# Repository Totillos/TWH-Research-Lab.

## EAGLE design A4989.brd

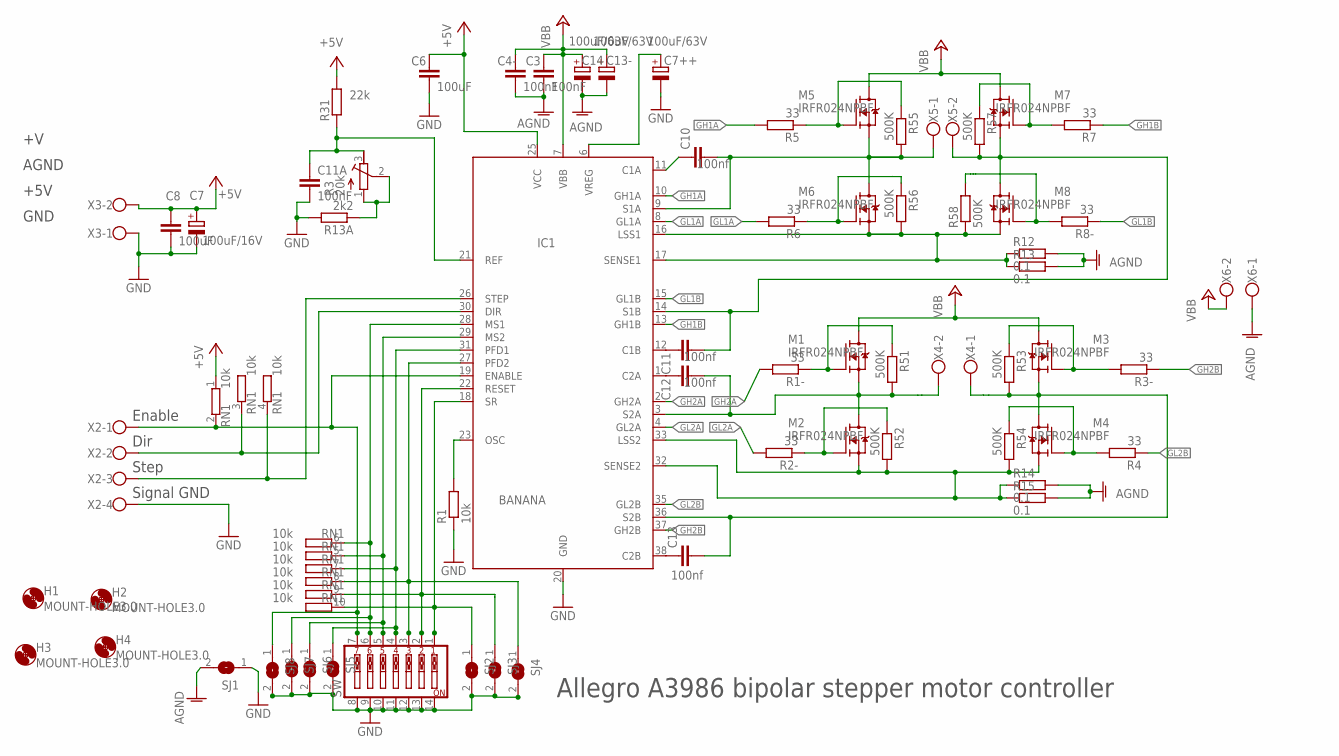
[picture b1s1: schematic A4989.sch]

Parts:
C3, C4-, C11A: 100nF; C0805
C6, C8: 100uF; C0805
C7: 100uF/16V; E5-10,5
C7++: 100uF/63V; E2-5
C10, C11, C12, C13: 100nf; C0805
C13-, C14: 100uF/63V; E5-10,5
H1, H2, H3, H4: MOUNT-HOLE3.0; 3,0
IC1: BANANA; TSSOP38
M1, M2, M3, M4, M5, M6, M7, M8: IRFR024NPBF; DPAK
R1: 10k; M0805
R1-, R2-, R3-, R4, R5, R6, R7, R8-: 33; R0805
R3: 20k; RTRIM64W
R12, R13, R14, R15: 0.1; R2512
R13A: 2k2; M0805
R31: 22k; M0805
R51, R52, R53, R54, R55, R56, R57, R58: 500K; R0805
RN1: 10k; SIL10
SJ1, SJ2, SJ3, SJ4, SJ5, SJ6, SJ7, SJ8: SJ
SW: SW_DIP-7; EDG-07
X2: W237-4
X3, X4, X5, X6: W237-102

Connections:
+5V: C6.1, C7.+, C8.1, IC1.25 (VCC), R31.2, RN1.1, X3.2
+24V: C3.1, C4-.1, C13-.+, C14.+, IC1.7 (VBB), M1.4 (D), M3.4 (D), M5.4 (D), M7.4 (D), X6.2
AGND: C3.2, C4-.2, C13-.-, C14.-, R12.2, R13.2, R14.2, R15.2, SJ1.2, X6.1
GH1A: IC1.10 (GH1A), R5.2
GH1B: IC1.13 (GH1B), R7.1
GH2A: IC1.2 (GH2A), R1-.2
GH2B: IC1.37 (GH2B), R3-.1
GL1A: IC1.8 (GL1A), R6.2
GL1B: IC1.15 (GL1B), R8-.1
GL2A: IC1.4 (GL2A), R2-.2
GL2B: IC1.35 (GL2B), R4.1
GND: C6.2, C7.-, C7++.-, C8.2, C11A.2, IC1.20 (GND), R1.1, R13A.2, SJ1.1, SJ2.2, SJ3.2, SJ4.2, SJ5.2, SJ6.2, SJ7.2, SJ8.2, SW.8, SW.9, SW.10, SW.11, SW.12, SW.13, SW.14, X2.4, X3.1
unnamed: IC1.27 (PFD2), RN1.8 (2), SJ4.1, SW.3
unnamed: R3.1 (E), R3.2 (S), R13A.1
unnamed: IC1.28 (MS1), RN1.6 (2), SJ7.1, SW.6
unnamed: C11A.1, IC1.21 (REF), R3.3 (A), R31.1
unnamed: IC1.29 (MS2), RN1.5 (2), SJ6.1, SW.5
unnamed: IC1.23 (OSC), R1.2
unnamed: C7++.+, IC1.6 (VREG)
unnamed: IC1.31 (PFD1), RN1.7 (2), SJ5.1, SW.4
unnamed: M5.1 (G), R5.1, R55.1
unnamed: IC1.16 (LSS1), IC1.17 (SENSE1), M6.3 (S), M8.3 (S), R12.1, R13.1, R56.2, R58.1
unnamed: IC1.32 (SENSE2), IC1.33 (LSS2), M2.3 (S), M4.3 (S), R14.1, R15.1, R52.2, R54.2
unnamed: M6.1 (G), R6.1, R56.1
unnamed: M8.1 (G), R8-.2, R58.2
unnamed: M7.1 (G), R7.2, R57.1
unnamed: M1.1 (G), R1-.1, R51.1
unnamed: IC1.18 (SR), RN1.10 (2), SJ2.1, SW.1
unnamed: M2.1 (G), R2-.1, R52.1
unnamed: IC1.22 (RESET), RN1.9 (2), SJ3.1, SW.2
unnamed: M4.1 (G), R4.2, R54.1
unnamed: M3.1 (G), R3-.2, R53.1
unnamed: IC1.26 (STEP), RN1.4 (2), X2.3
unnamed: C10.2, IC1.9 (S1A), M5.3 (S), M6.4 (D), R55.2, X5.1
unnamed: IC1.30 (DIR), RN1.3 (2), X2.2
unnamed: C11.2, IC1.14 (S1B), M7.3 (S), M8.4 (D), R57.2, X5.2
unnamed: C12.2, IC1.3 (S2A), M1.3 (S), M2.4 (D), R51.2, X4.2
unnamed: C13.2, IC1.36 (S2B), M3.3 (S), M4.4 (D), R53.2, X4.1
unnamed: IC1.19 (ENABLE), RN1.2, SJ8.1, SW.7, X2.1
unnamed: C10.1, IC1.11 (C1A)
unnamed: C11.1, IC1.12 (C1B)
unnamed: C12.1, IC1.1 (C2A)
unnamed: C13.1, IC1.38 (C2B)

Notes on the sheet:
Enable
Dir
Step
Signal GND
Allegro A3986 bipolar stepper motor controller
+5V
GND
AGND

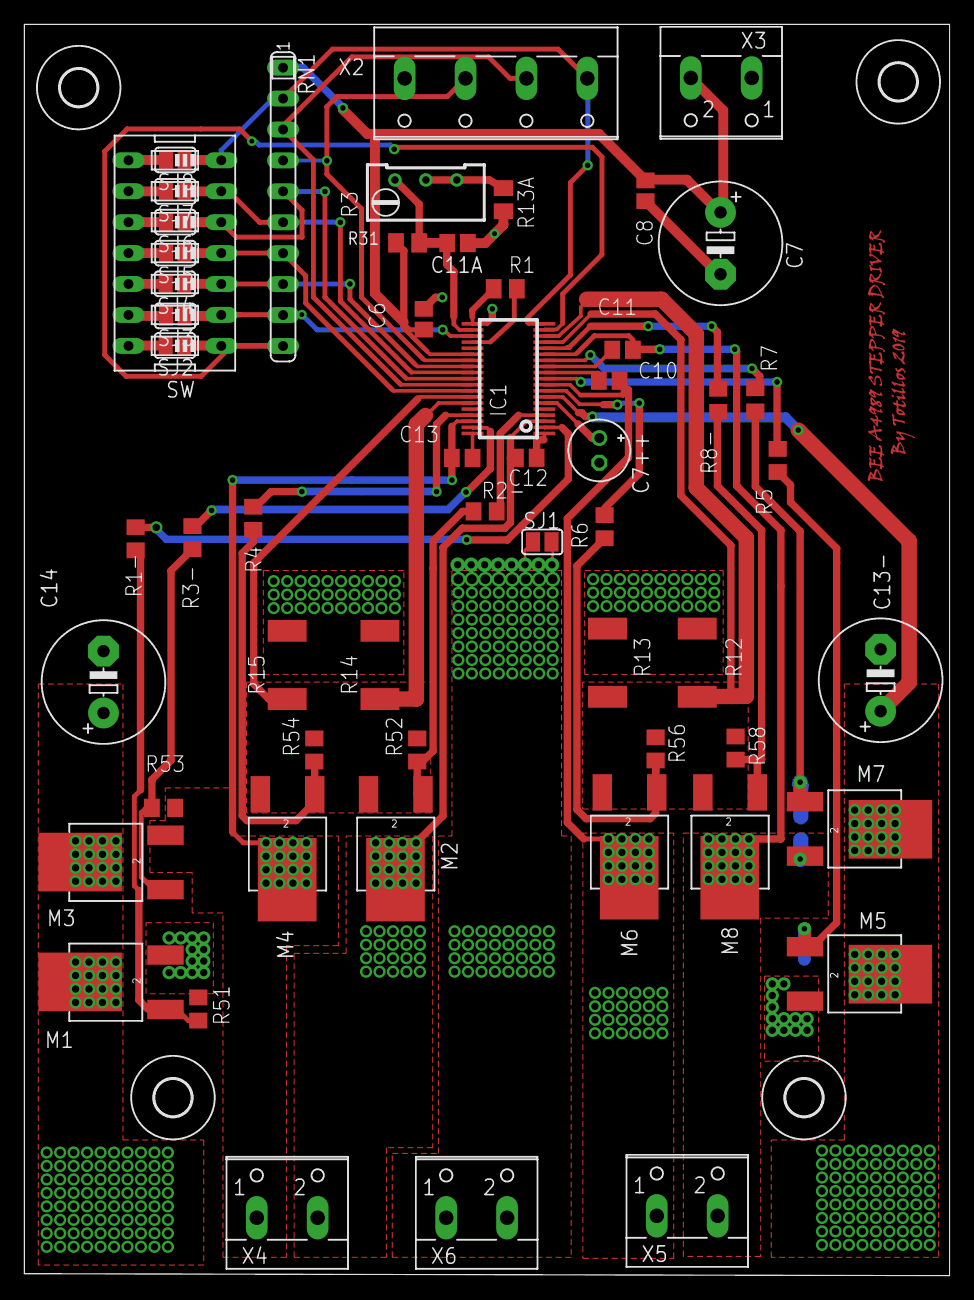
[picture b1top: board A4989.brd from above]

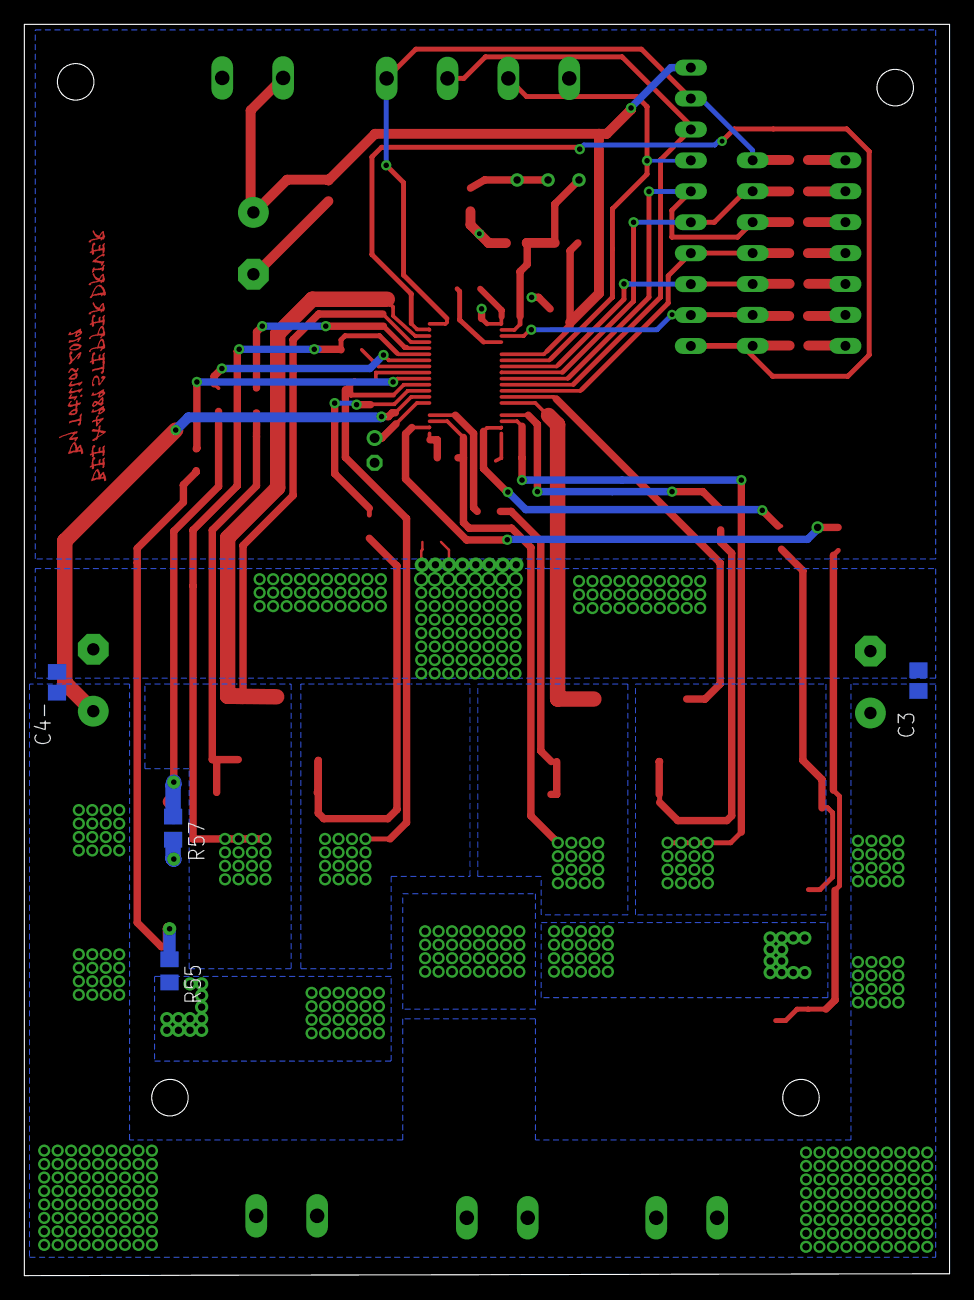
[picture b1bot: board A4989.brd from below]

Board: 2 copper layers, 76.0 x 102.8 mm, 65 parts (4 on the bottom side), 43 nets.

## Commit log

2018-12-24 Create ALLEGRO A4889 BOARD FOR BIPOLAR STEPPER MOTOR AP TO 500W
    Board + schematic in EAGLE format
